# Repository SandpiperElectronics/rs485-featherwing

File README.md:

This featherwing PCB allows for long-distance communication between feather microcontrollers. This board implements an RS-485 network with bidirectional communication. RS-485 was selected over other twisted pair protocols due to it having no defined software protocol. 
This featherwing uses a Texas Instruments THVD1424RGTR RS-485 Driver. The THVD1424RGTR driver allows for a single PCB design to implement both endpoints and midpoints in our network. Additionally this board is compatible with the Adafruit Feather microcontroller development board format.

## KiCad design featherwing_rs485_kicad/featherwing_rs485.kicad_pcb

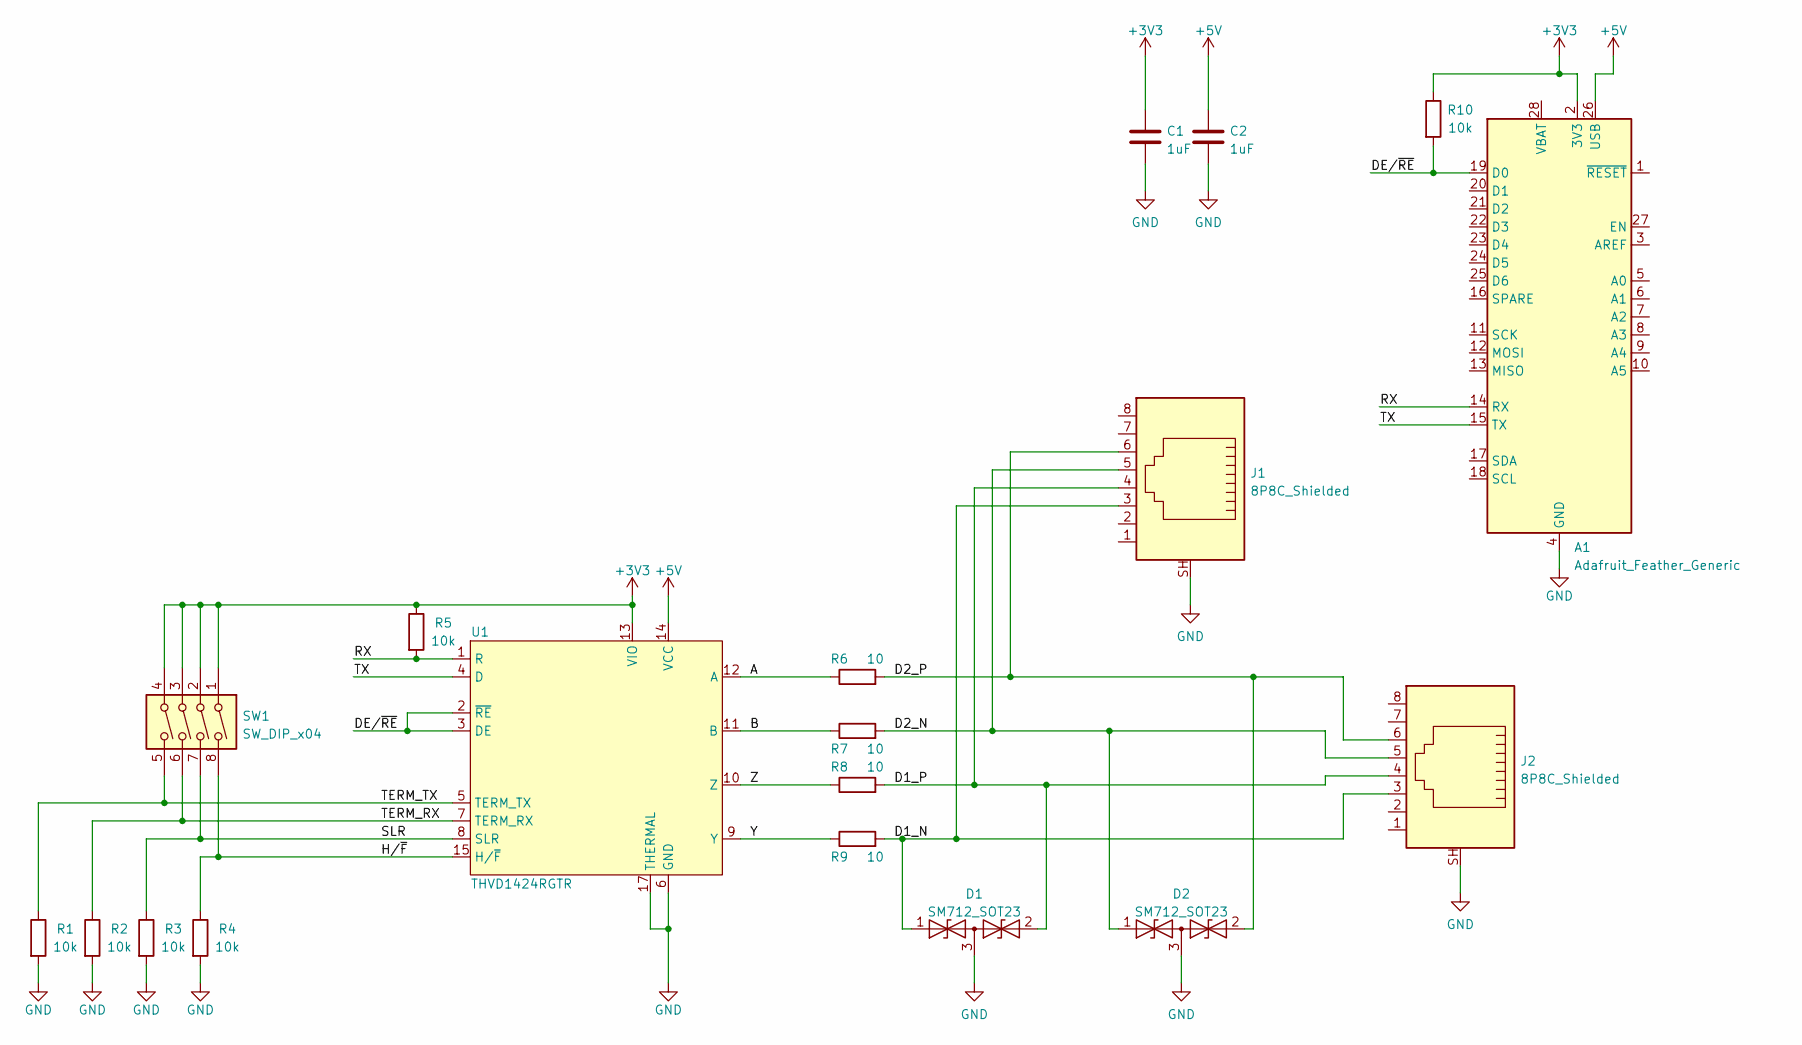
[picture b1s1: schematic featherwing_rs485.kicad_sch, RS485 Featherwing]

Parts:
A1: Adafruit_Feather_Generic; Adafruit_Feather
C1, C2: 1uF; R_0603_1608Metric
D1, D2: SM712_SOT23; SOT-23
J1, J2: 8P8C_Shielded; 0955406888-MOLEX
R1, R2, R3, R4, R5, R10: 10k; R_0603_1608Metric
R6, R7, R8, R9: 10; R_0603_1608Metric
SW1: SW_DIP_x04; SW_DIP_SPSTx04_Slide_6.7x11.72mm_W6.73mm_P2.54mm_LowProfile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
U1: THVD1424RGTR; VQFN-16-1EP_3x3mm_P0.5mm_EP1.8x1.8mm_ThermalVias

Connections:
+3V3: A1.2 (3V3), C1.1, R5.1, R10.1, SW1.1, SW1.2, SW1.3, SW1.4, U1.13 (VIO)
+5V: A1.26 (USB), C2.1, U1.14 (VCC)
/A: R6.1, U1.12 (A)
/B: R7.1, U1.11 (B)
/D1_N: D1.1 (A1), J1.3, J2.3, R9.2
/D1_P: D1.2 (A2), J1.4, J2.4, R8.2
/D2_N: D2.1 (A1), J1.5, J2.5, R7.2
/D2_P: D2.2 (A2), J1.6, J2.6, R6.2
/DE/~RE: A1.19 (D0), R10.2, U1.2 (~RE), U1.3 (DE)
/H/~F: R4.1, SW1.8, U1.15 (H/~F)
/RX: A1.14 (RX), R5.2, U1.1 (R)
/SLR: R3.1, SW1.7, U1.8 (SLR)
/TERM_RX: R2.1, SW1.6, U1.7 (TERM_RX)
/TERM_TX: R1.1, SW1.5, U1.5 (TERM_TX)
/TX: A1.15 (TX), U1.4 (D)
/Y: R9.1, U1.9 (Y)
/Z: R8.1, U1.10 (Z)
GND: A1.4 (GND), C1.2, C2.2, D1.3 (common), D2.3 (common), J1.SH, J2.SH, R1.2, R2.2, R3.2, R4.2, U1.6 (GND), U1.17 (THERMAL)

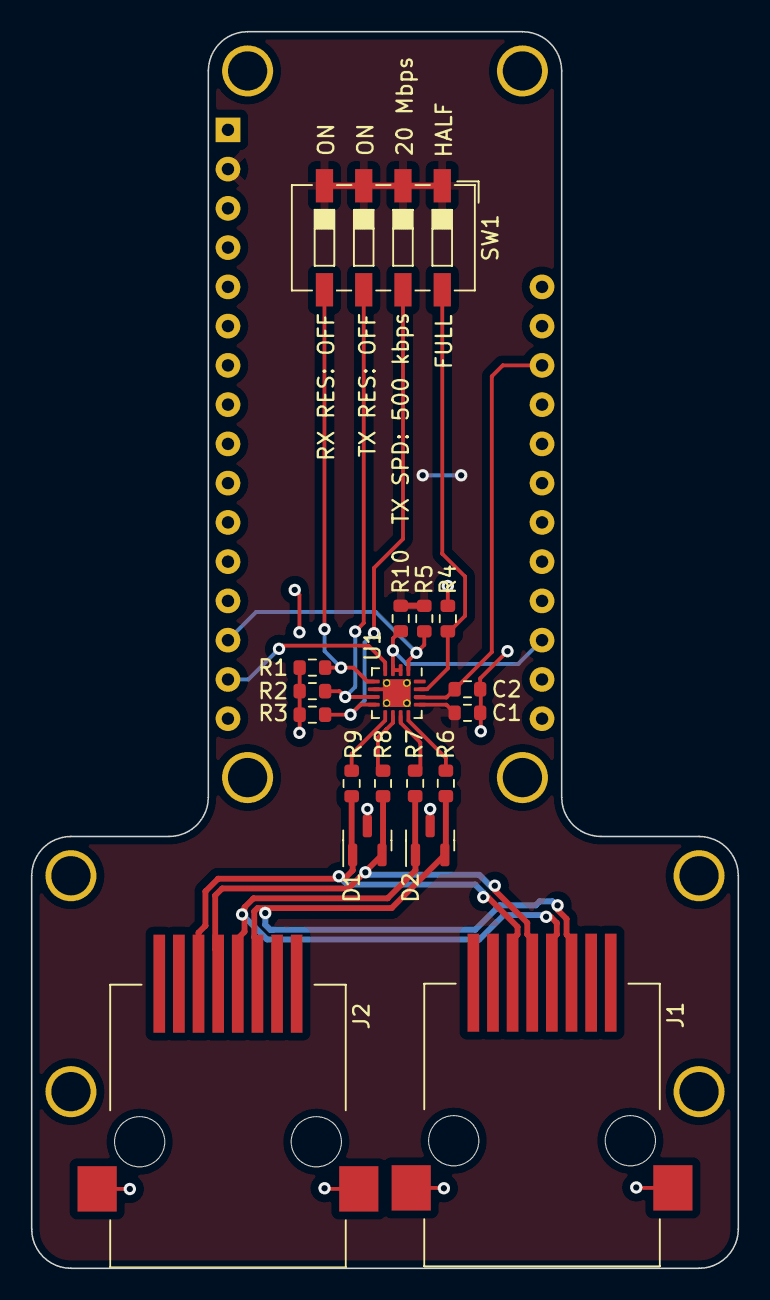
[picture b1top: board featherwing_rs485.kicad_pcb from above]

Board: 2 copper layers, 45.7 x 80.0 mm, 19 parts (0 on the bottom side), 18 nets.
